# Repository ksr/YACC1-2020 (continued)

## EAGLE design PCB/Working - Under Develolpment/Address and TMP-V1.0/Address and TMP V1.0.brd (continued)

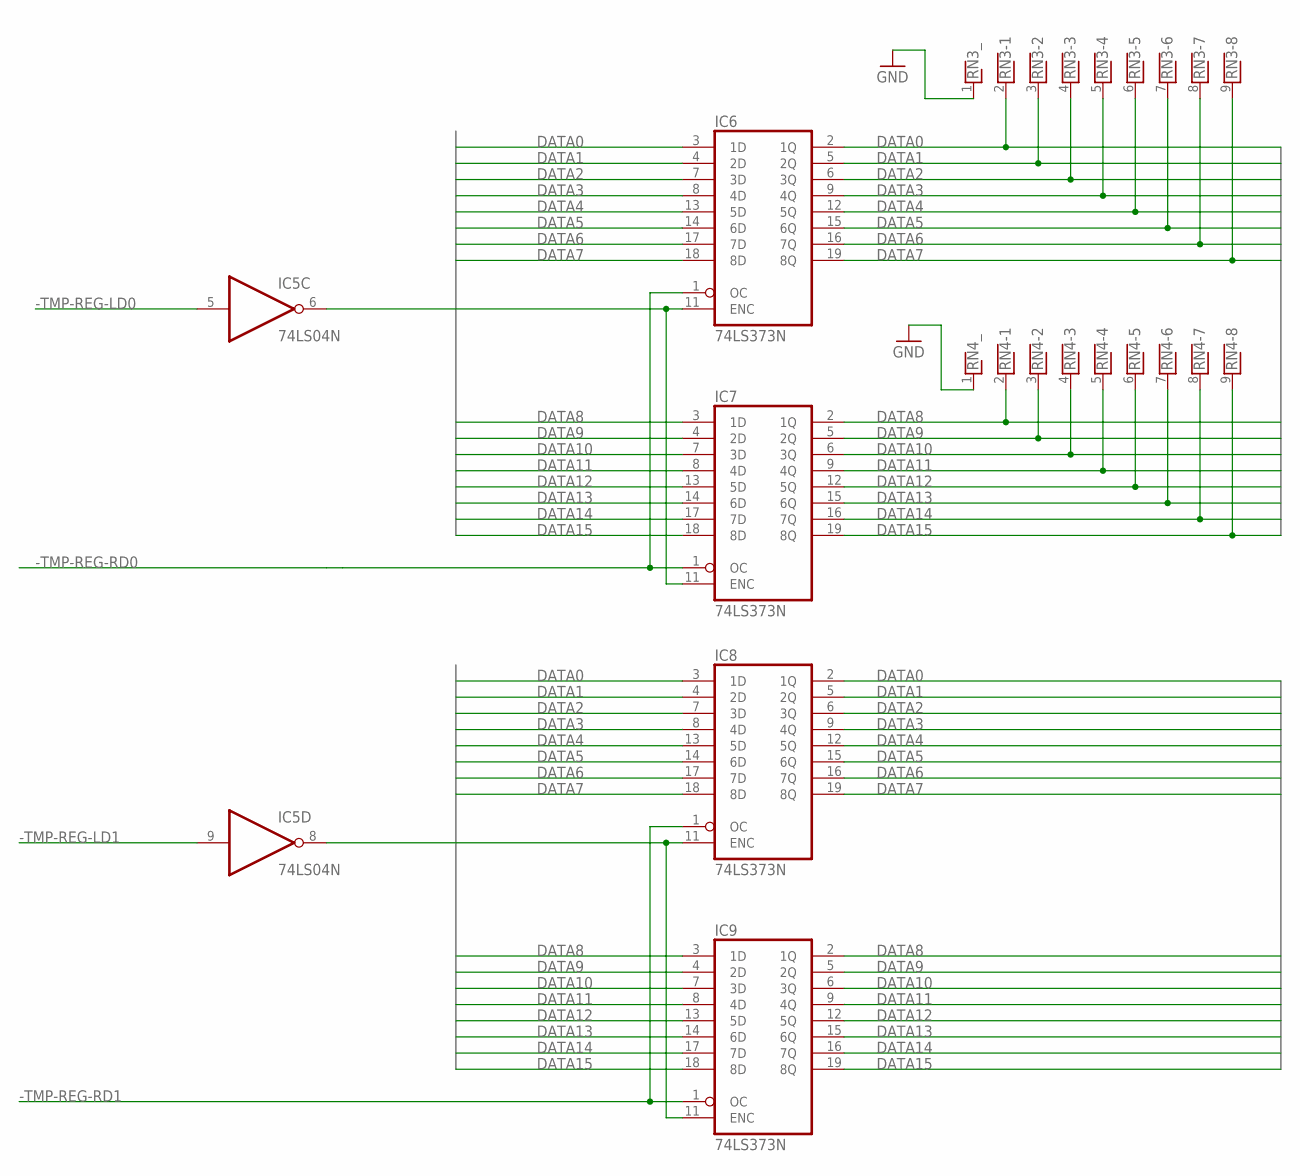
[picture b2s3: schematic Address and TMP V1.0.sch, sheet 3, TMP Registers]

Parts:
IC5: 74LS04N; DIL14
IC6, IC7, IC8, IC9: 74LS373N; DIL20
RN3, RN4: RNX8; RN-9

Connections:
-TMP-REG-LD0: IC5.5 (I); also elsewhere on the board
-TMP-REG-LD1: IC5.9 (I); also elsewhere on the board
-TMP-REG-RD0: IC6.1 (OC), IC7.1 (OC); also elsewhere on the board
-TMP-REG-RD1: IC8.1 (OC), IC9.1 (OC); also elsewhere on the board
DATA0: IC6.2 (1Q), IC6.3 (1D), IC8.2 (1Q), IC8.3 (1D), RN3.2; also elsewhere on the board
DATA1: IC6.4 (2D), IC6.5 (2Q), IC8.4 (2D), IC8.5 (2Q), RN3.3; also elsewhere on the board
DATA2: IC6.6 (3Q), IC6.7 (3D), IC8.6 (3Q), IC8.7 (3D), RN3.4; also elsewhere on the board
DATA3: IC6.8 (4D), IC6.9 (4Q), IC8.8 (4D), IC8.9 (4Q), RN3.5; also elsewhere on the board
DATA4: IC6.12 (5Q), IC6.13 (5D), IC8.12 (5Q), IC8.13 (5D), RN3.6; also elsewhere on the board
DATA5: IC6.14 (6D), IC6.15 (6Q), IC8.14 (6D), IC8.15 (6Q), RN3.7; also elsewhere on the board
DATA6: IC6.16 (7Q), IC6.17 (7D), IC8.16 (7Q), IC8.17 (7D), RN3.8; also elsewhere on the board
DATA7: IC6.18 (8D), IC6.19 (8Q), IC8.18 (8D), IC8.19 (8Q), RN3.9; also elsewhere on the board
DATA8: IC7.2 (1Q), IC7.3 (1D), IC9.2 (1Q), IC9.3 (1D), RN4.2; also elsewhere on the board
DATA9: IC7.4 (2D), IC7.5 (2Q), IC9.4 (2D), IC9.5 (2Q), RN4.3; also elsewhere on the board
DATA10: IC7.6 (3Q), IC7.7 (3D), IC9.6 (3Q), IC9.7 (3D), RN4.4; also elsewhere on the board
DATA11: IC7.8 (4D), IC7.9 (4Q), IC9.8 (4D), IC9.9 (4Q), RN4.5; also elsewhere on the board
DATA12: IC7.12 (5Q), IC7.13 (5D), IC9.12 (5Q), IC9.13 (5D), RN4.6; also elsewhere on the board
DATA13: IC7.14 (6D), IC7.15 (6Q), IC9.14 (6D), IC9.15 (6Q), RN4.7; also elsewhere on the board
DATA14: IC7.16 (7Q), IC7.17 (7D), IC9.16 (7Q), IC9.17 (7D), RN4.8; also elsewhere on the board
DATA15: IC7.18 (8D), IC7.19 (8Q), IC9.18 (8D), IC9.19 (8Q), RN4.9; also elsewhere on the board
GND: IC5.7 (GND), IC6.10 (GND), IC7.10 (GND), IC8.10 (GND), IC9.10 (GND), RN3.1, RN4.1; also elsewhere on the board
unnamed: IC5.6 (O), IC6.11 (ENC), IC7.11 (ENC)
unnamed: IC5.8 (O), IC8.11 (ENC), IC9.11 (ENC)
VCC: IC5.14 (VCC), IC6.20 (VCC), IC7.20 (VCC), IC8.20 (VCC), IC9.20 (VCC); also elsewhere on the board

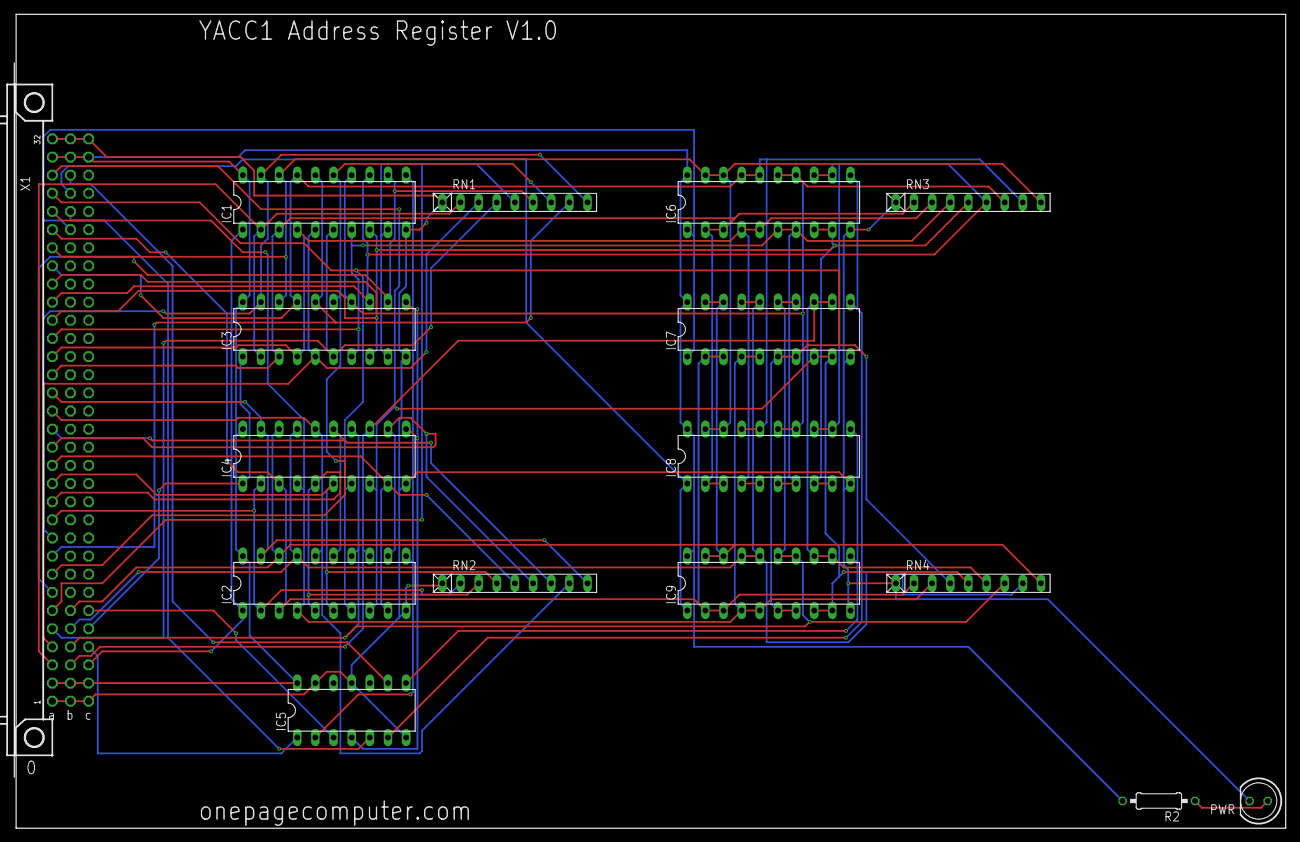
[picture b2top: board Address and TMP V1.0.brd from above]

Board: 2 copper layers, 177.8 x 114.0 mm, 16 parts (0 on the bottom side), 47 nets.

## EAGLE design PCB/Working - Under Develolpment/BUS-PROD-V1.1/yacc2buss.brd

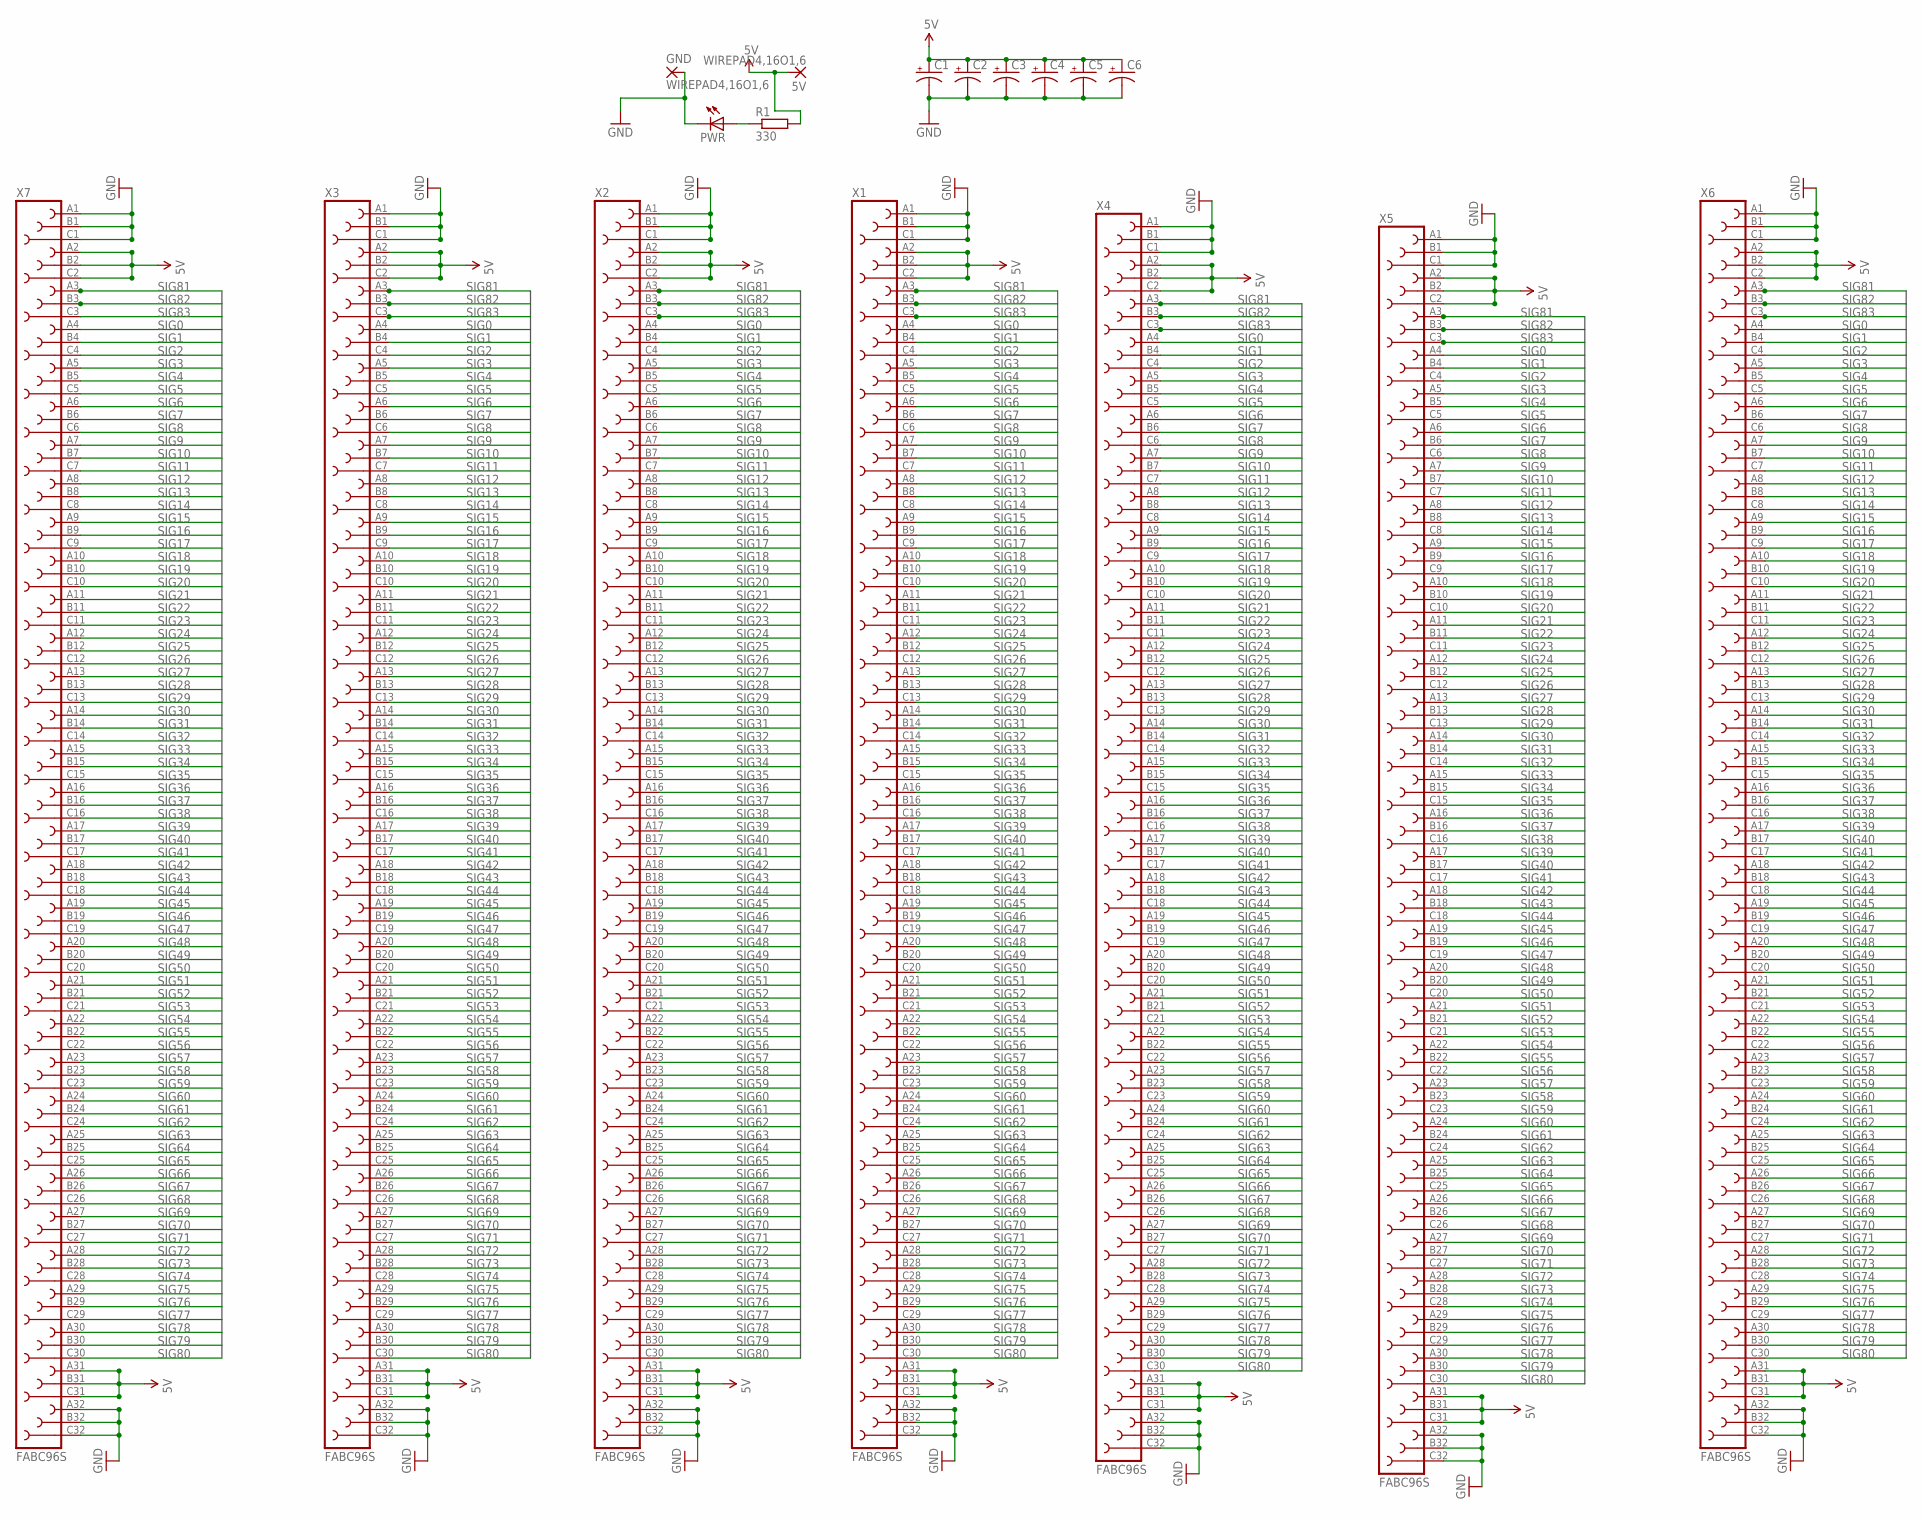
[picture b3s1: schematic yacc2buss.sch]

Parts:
5V: WIREPAD4,16O1,6; 4,16O1,6
C1, C2, C3, C4, C5, C6: CPOL-USE5-6; E5-6
GND: WIREPAD4,16O1,6; 4,16O1,6
PWR: LED5MM
R1: 330; 0207/10
X1, X2, X3, X4, X5, X6, X7: FABC96S

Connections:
5V: 5V.1, C1.+, C2.+, C3.+, C4.+, C5.+, C6.+, R1.2, X1.A2, X1.A31, X1.B2, X1.B31, X1.C2, X1.C31, X2.A2, X2.A31, X2.B2, X2.B31, X2.C2, X2.C31, X3.A2, X3.A31, X3.B2, X3.B31, X3.C2, X3.C31, X4.A2, X4.A31, X4.B2, X4.B31, X4.C2, X4.C31, X5.A2, X5.A31, X5.B2, X5.B31, X5.C2, X5.C31, X6.A2, X6.A31, X6.B2, X6.B31, X6.C2, X6.C31, X7.A2, X7.A31, X7.B2, X7.B31, X7.C2, X7.C31
GND: C1.-, C2.-, C3.-, C4.-, C5.-, C6.-, GND.1, PWR.K (C), X1.A1, X1.A32, X1.B1, X1.B32, X1.C1, X1.C32, X2.A1, X2.A32, X2.B1, X2.B32, X2.C1, X2.C32, X3.A1, X3.A32, X3.B1, X3.B32, X3.C1, X3.C32, X4.A1, X4.A32, X4.B1, X4.B32, X4.C1, X4.C32, X5.A1, X5.A32, X5.B1, X5.B32, X5.C1, X5.C32, X6.A1, X6.A32, X6.B1, X6.B32, X6.C1, X6.C32, X7.A1, X7.A32, X7.B1, X7.B32, X7.C1, X7.C32
unnamed: PWR.A, R1.1
SIG0: X1.A4, X2.A4, X3.A4, X4.A4, X5.A4, X6.A4, X7.A4
SIG1: X1.B4, X2.B4, X3.B4, X4.B4, X5.B4, X6.B4, X7.B4
SIG2: X1.C4, X2.C4, X3.C4, X4.C4, X5.C4, X6.C4, X7.C4
SIG3: X1.A5, X2.A5, X3.A5, X4.A5, X5.A5, X6.A5, X7.A5
SIG4: X1.B5, X2.B5, X3.B5, X4.B5, X5.B5, X6.B5, X7.B5
SIG5: X1.C5, X2.C5, X3.C5, X4.C5, X5.C5, X6.C5, X7.C5
SIG6: X1.A6, X2.A6, X3.A6, X4.A6, X5.A6, X6.A6, X7.A6
SIG7: X1.B6, X2.B6, X3.B6, X4.B6, X5.B6, X6.B6, X7.B6
SIG8: X1.C6, X2.C6, X3.C6, X4.C6, X5.C6, X6.C6, X7.C6
SIG9: X1.A7, X2.A7, X3.A7, X4.A7, X5.A7, X6.A7, X7.A7
SIG10: X1.B7, X2.B7, X3.B7, X4.B7, X5.B7, X6.B7, X7.B7
SIG11: X1.C7, X2.C7, X3.C7, X4.C7, X5.C7, X6.C7, X7.C7
SIG12: X1.A8, X2.A8, X3.A8, X4.A8, X5.A8, X6.A8, X7.A8
SIG13: X1.B8, X2.B8, X3.B8, X4.B8, X5.B8, X6.B8, X7.B8
SIG14: X1.C8, X2.C8, X3.C8, X4.C8, X5.C8, X6.C8, X7.C8
SIG15: X1.A9, X2.A9, X3.A9, X4.A9, X5.A9, X6.A9, X7.A9
SIG16: X1.B9, X2.B9, X3.B9, X4.B9, X5.B9, X6.B9, X7.B9
SIG17: X1.C9, X2.C9, X3.C9, X4.C9, X5.C9, X6.C9, X7.C9
SIG18: X1.A10, X2.A10, X3.A10, X4.A10, X5.A10, X6.A10, X7.A10
SIG19: X1.B10, X2.B10, X3.B10, X4.B10, X5.B10, X6.B10, X7.B10
SIG20: X1.C10, X2.C10, X3.C10, X4.C10, X5.C10, X6.C10, X7.C10
SIG21: X1.A11, X2.A11, X3.A11, X4.A11, X5.A11, X6.A11, X7.A11
SIG22: X1.B11, X2.B11, X3.B11, X4.B11, X5.B11, X6.B11, X7.B11
SIG23: X1.C11, X2.C11, X3.C11, X4.C11, X5.C11, X6.C11, X7.C11
SIG24: X1.A12, X2.A12, X3.A12, X4.A12, X5.A12, X6.A12, X7.A12
SIG25: X1.B12, X2.B12, X3.B12, X4.B12, X5.B12, X6.B12, X7.B12
SIG26: X1.C12, X2.C12, X3.C12, X4.C12, X5.C12, X6.C12, X7.C12
SIG27: X1.A13, X2.A13, X3.A13, X4.A13, X5.A13, X6.A13, X7.A13
SIG28: X1.B13, X2.B13, X3.B13, X4.B13, X5.B13, X6.B13, X7.B13
SIG29: X1.C13, X2.C13, X3.C13, X4.C13, X5.C13, X6.C13, X7.C13
SIG30: X1.A14, X2.A14, X3.A14, X4.A14, X5.A14, X6.A14, X7.A14
SIG31: X1.B14, X2.B14, X3.B14, X4.B14, X5.B14, X6.B14, X7.B14
SIG32: X1.C14, X2.C14, X3.C14, X4.C14, X5.C14, X6.C14, X7.C14
SIG33: X1.A15, X2.A15, X3.A15, X4.A15, X5.A15, X6.A15, X7.A15
SIG34: X1.B15, X2.B15, X3.B15, X4.B15, X5.B15, X6.B15, X7.B15
SIG35: X1.C15, X2.C15, X3.C15, X4.C15, X5.C15, X6.C15, X7.C15
SIG36: X1.A16, X2.A16, X3.A16, X4.A16, X5.A16, X6.A16, X7.A16
SIG37: X1.B16, X2.B16, X3.B16, X4.B16, X5.B16, X6.B16, X7.B16
SIG38: X1.C16, X2.C16, X3.C16, X4.C16, X5.C16, X6.C16, X7.C16
SIG39: X1.A17, X2.A17, X3.A17, X4.A17, X5.A17, X6.A17, X7.A17
SIG40: X1.B17, X2.B17, X3.B17, X4.B17, X5.B17, X6.B17, X7.B17
SIG41: X1.C17, X2.C17, X3.C17, X4.C17, X5.C17, X6.C17, X7.C17
SIG42: X1.A18, X2.A18, X3.A18, X4.A18, X5.A18, X6.A18, X7.A18
SIG43: X1.B18, X2.B18, X3.B18, X4.B18, X5.B18, X6.B18, X7.B18
SIG44: X1.C18, X2.C18, X3.C18, X4.C18, X5.C18, X6.C18, X7.C18
SIG45: X1.A19, X2.A19, X3.A19, X4.A19, X5.A19, X6.A19, X7.A19
SIG46: X1.B19, X2.B19, X3.B19, X4.B19, X5.B19, X6.B19, X7.B19
SIG47: X1.C19, X2.C19, X3.C19, X4.C19, X5.C19, X6.C19, X7.C19
SIG48: X1.A20, X2.A20, X3.A20, X4.A20, X5.A20, X6.A20, X7.A20
SIG49: X1.B20, X2.B20, X3.B20, X4.B20, X5.B20, X6.B20, X7.B20
SIG50: X1.C20, X2.C20, X3.C20, X4.C20, X5.C20, X6.C20, X7.C20
SIG51: X1.A21, X2.A21, X3.A21, X4.A21, X5.A21, X6.A21, X7.A21
SIG52: X1.B21, X2.B21, X3.B21, X4.B21, X5.B21, X6.B21, X7.B21
SIG53: X1.C21, X2.C21, X3.C21, X4.C21, X5.C21, X6.C21, X7.C21
SIG54: X1.A22, X2.A22, X3.A22, X4.A22, X5.A22, X6.A22, X7.A22
SIG55: X1.B22, X2.B22, X3.B22, X4.B22, X5.B22, X6.B22, X7.B22
SIG56: X1.C22, X2.C22, X3.C22, X4.C22, X5.C22, X6.C22, X7.C22
SIG57: X1.A23, X2.A23, X3.A23, X4.A23, X5.A23, X6.A23, X7.A23
SIG58: X1.B23, X2.B23, X3.B23, X4.B23, X5.B23, X6.B23, X7.B23
SIG59: X1.C23, X2.C23, X3.C23, X4.C23, X5.C23, X6.C23, X7.C23
SIG60: X1.A24, X2.A24, X3.A24, X4.A24, X5.A24, X6.A24, X7.A24
SIG61: X1.B24, X2.B24, X3.B24, X4.B24, X5.B24, X6.B24, X7.B24
SIG62: X1.C24, X2.C24, X3.C24, X4.C24, X5.C24, X6.C24, X7.C24
SIG63: X1.A25, X2.A25, X3.A25, X4.A25, X5.A25, X6.A25, X7.A25
SIG64: X1.B25, X2.B25, X3.B25, X4.B25, X5.B25, X6.B25, X7.B25
SIG65: X1.C25, X2.C25, X3.C25, X4.C25, X5.C25, X6.C25, X7.C25
SIG66: X1.A26, X2.A26, X3.A26, X4.A26, X5.A26, X6.A26, X7.A26
SIG67: X1.B26, X2.B26, X3.B26, X4.B26, X5.B26, X6.B26, X7.B26
SIG68: X1.C26, X2.C26, X3.C26, X4.C26, X5.C26, X6.C26, X7.C26
SIG69: X1.A27, X2.A27, X3.A27, X4.A27, X5.A27, X6.A27, X7.A27
SIG70: X1.B27, X2.B27, X3.B27, X4.B27, X5.B27, X6.B27, X7.B27
SIG71: X1.C27, X2.C27, X3.C27, X4.C27, X5.C27, X6.C27, X7.C27
SIG72: X1.A28, X2.A28, X3.A28, X4.A28, X5.A28, X6.A28, X7.A28
SIG73: X1.B28, X2.B28, X3.B28, X4.B28, X5.B28, X6.B28, X7.B28
SIG74: X1.C28, X2.C28, X3.C28, X4.C28, X5.C28, X6.C28, X7.C28
SIG75: X1.A29, X2.A29, X3.A29, X4.A29, X5.A29, X6.A29, X7.A29
SIG76: X1.B29, X2.B29, X3.B29, X4.B29, X5.B29, X6.B29, X7.B29
SIG77: X1.C29, X2.C29, X3.C29, X4.C29, X5.C29, X6.C29, X7.C29
SIG78: X1.A30, X2.A30, X3.A30, X4.A30, X5.A30, X6.A30, X7.A30
SIG79: X1.B30, X2.B30, X3.B30, X4.B30, X5.B30, X6.B30, X7.B30
SIG80: X1.C30, X2.C30, X3.C30, X4.C30, X5.C30, X6.C30, X7.C30
SIG81: X1.A3, X2.A3, X3.A3, X4.A3, X5.A3, X6.A3, X7.A3
SIG82: X1.B3, X2.B3, X3.B3, X4.B3, X5.B3, X6.B3, X7.B3
SIG83: X1.C3, X2.C3, X3.C3, X4.C3, X5.C3, X6.C3, X7.C3

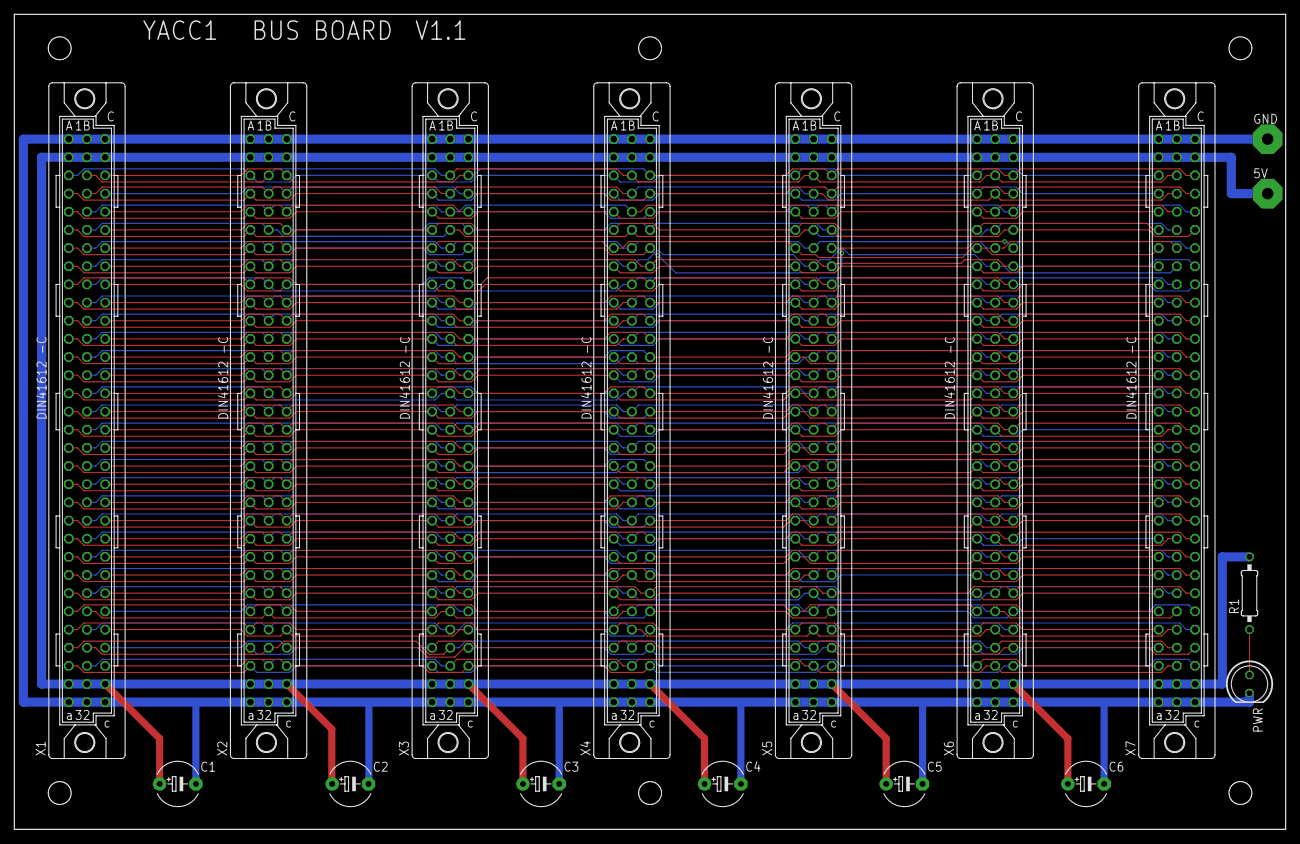
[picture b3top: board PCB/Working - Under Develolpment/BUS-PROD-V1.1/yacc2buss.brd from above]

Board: 2 copper layers, 177.8 x 114.0 mm, 17 parts (0 on the bottom side), 87 nets.

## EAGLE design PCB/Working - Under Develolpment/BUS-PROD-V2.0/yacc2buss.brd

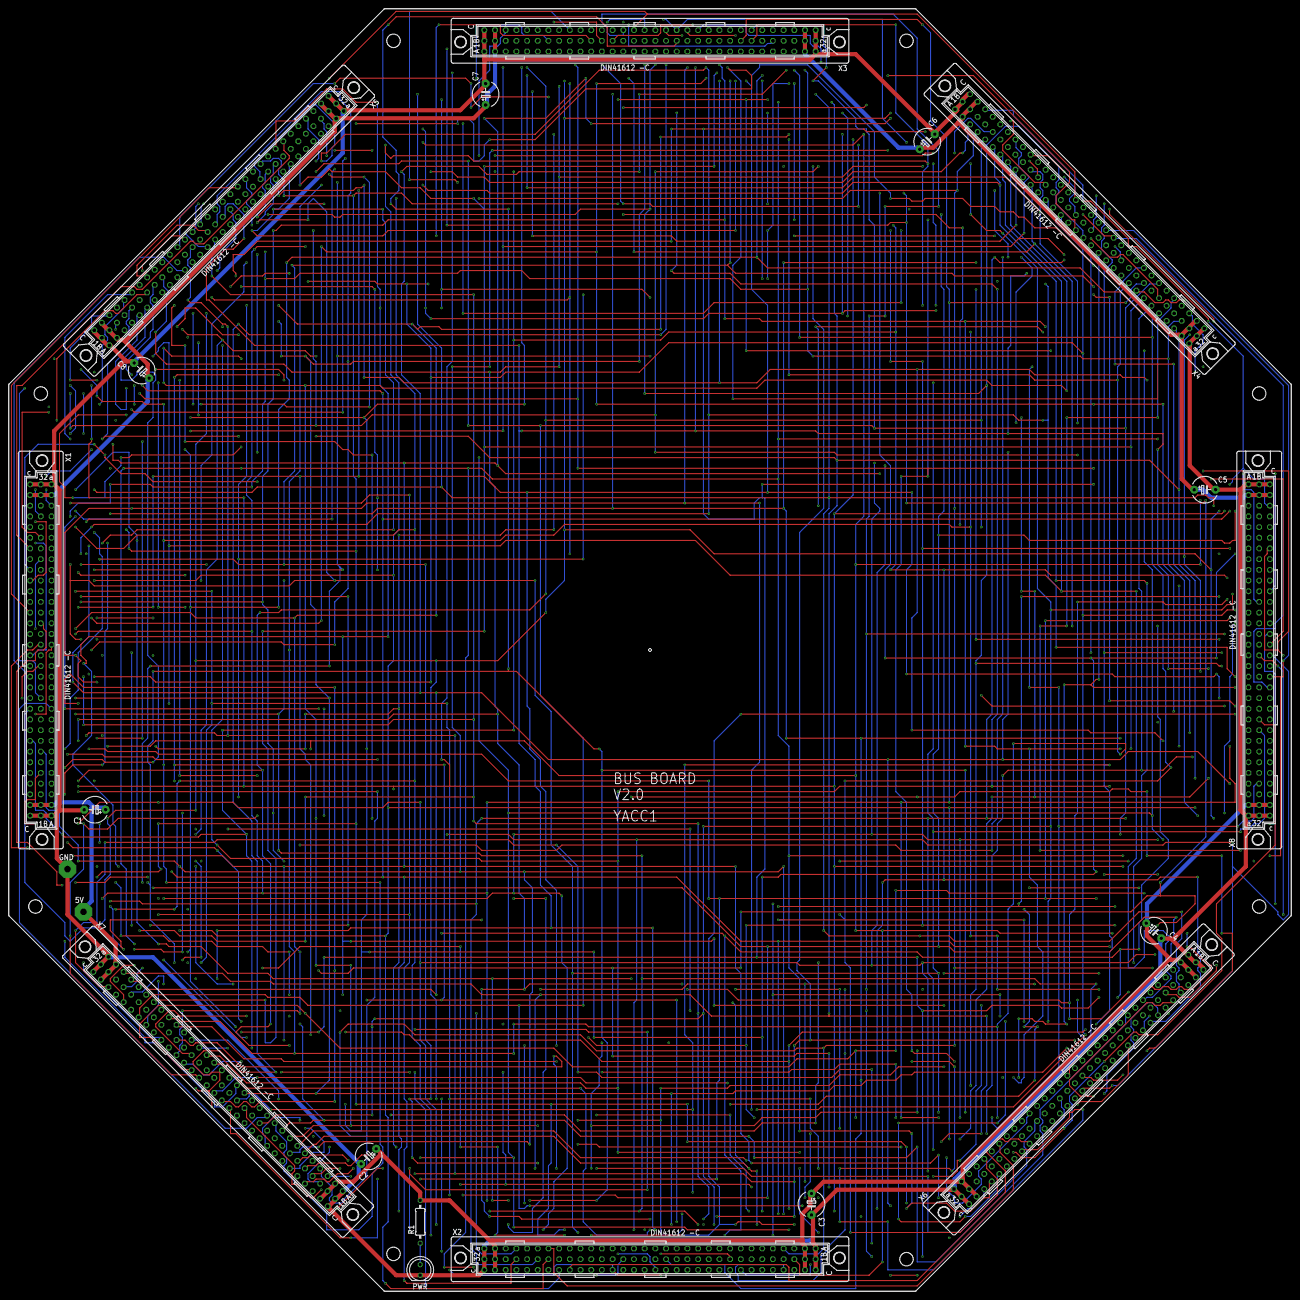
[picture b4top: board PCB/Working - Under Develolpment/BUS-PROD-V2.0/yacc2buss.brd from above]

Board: 4 copper layers, 304.8 x 304.8 mm, 20 parts (0 on the bottom side), 87 nets.

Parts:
5V: WIREPAD4,16O1,6; 4,16O1,6
C1, C2, C3, C4, C5, C6, C7, C8: E5-6
GND: WIREPAD4,16O1,6; 4,16O1,6
PWR: LED5MM
R1: 330; 0207/10
X1, X2, X3, X4, X5, X6, X7, X8: FABC96S

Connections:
5V: 5V.1, C1.+, C2.+, C3.+, C4.+, C5.+, C6.+, C7.+, C8.+, R1.2, X1.A2, X1.A31, X1.B2, X1.B31, X1.C2, X1.C31, X2.A2, X2.A31, X2.B2, X2.B31, X2.C2, X2.C31, X3.A2, X3.A31, X3.B2, X3.B31, X3.C2, X3.C31, X4.A2, X4.A31, X4.B2, X4.B31, X4.C2, X4.C31, X5.A2, X5.A31, X5.B2, X5.B31, X5.C2, X5.C31, X6.A2, X6.A31, X6.B2, X6.B31, X6.C2, X6.C31, X7.A2, X7.A31, X7.B2, X7.B31, X7.C2, X7.C31, X8.A2, X8.A31, X8.B2, X8.B31, X8.C2, X8.C31
GND: C1.-, C2.-, C3.-, C4.-, C5.-, C6.-, C7.-, C8.-, GND.1, PWR.K, X1.A1, X1.A32, X1.B1, X1.B32, X1.C1, X1.C32, X2.A1, X2.A32, X2.B1, X2.B32, X2.C1, X2.C32, X3.A1, X3.A32, X3.B1, X3.B32, X3.C1, X3.C32, X4.A1, X4.A32, X4.B1, X4.B32, X4.C1, X4.C32, X5.A1, X5.A32, X5.B1, X5.B32, X5.C1, X5.C32, X6.A1, X6.A32, X6.B1, X6.B32, X6.C1, X6.C32, X7.A1, X7.A32, X7.B1, X7.B32, X7.C1, X7.C32, X8.A1, X8.A32, X8.B1, X8.B32, X8.C1, X8.C32
unnamed: PWR.A, R1.1
SIG0: X1.A4, X2.A4, X3.A4, X4.A4, X5.A4, X6.A4, X7.A4, X8.A4
SIG1: X1.B4, X2.B4, X3.B4, X4.B4, X5.B4, X6.B4, X7.B4, X8.B4
SIG2: X1.C4, X2.C4, X3.C4, X4.C4, X5.C4, X6.C4, X7.C4, X8.C4
SIG3: X1.A5, X2.A5, X3.A5, X4.A5, X5.A5, X6.A5, X7.A5, X8.A5
SIG4: X1.B5, X2.B5, X3.B5, X4.B5, X5.B5, X6.B5, X7.B5, X8.B5
SIG5: X1.C5, X2.C5, X3.C5, X4.C5, X5.C5, X6.C5, X7.C5, X8.C5
SIG6: X1.A6, X2.A6, X3.A6, X4.A6, X5.A6, X6.A6, X7.A6, X8.A6
SIG7: X1.B6, X2.B6, X3.B6, X4.B6, X5.B6, X6.B6, X7.B6, X8.B6
SIG8: X1.C6, X2.C6, X3.C6, X4.C6, X5.C6, X6.C6, X7.C6, X8.C6
SIG9: X1.A7, X2.A7, X3.A7, X4.A7, X5.A7, X6.A7, X7.A7, X8.A7
SIG10: X1.B7, X2.B7, X3.B7, X4.B7, X5.B7, X6.B7, X7.B7, X8.B7
SIG11: X1.C7, X2.C7, X3.C7, X4.C7, X5.C7, X6.C7, X7.C7, X8.C7
SIG12: X1.A8, X2.A8, X3.A8, X4.A8, X5.A8, X6.A8, X7.A8, X8.A8
SIG13: X1.B8, X2.B8, X3.B8, X4.B8, X5.B8, X6.B8, X7.B8, X8.B8
SIG14: X1.C8, X2.C8, X3.C8, X4.C8, X5.C8, X6.C8, X7.C8, X8.C8
SIG15: X1.A9, X2.A9, X3.A9, X4.A9, X5.A9, X6.A9, X7.A9, X8.A9
SIG16: X1.B9, X2.B9, X3.B9, X4.B9, X5.B9, X6.B9, X7.B9, X8.B9
SIG17: X1.C9, X2.C9, X3.C9, X4.C9, X5.C9, X6.C9, X7.C9, X8.C9
SIG18: X1.A10, X2.A10, X3.A10, X4.A10, X5.A10, X6.A10, X7.A10, X8.A10
SIG19: X1.B10, X2.B10, X3.B10, X4.B10, X5.B10, X6.B10, X7.B10, X8.B10
SIG20: X1.C10, X2.C10, X3.C10, X4.C10, X5.C10, X6.C10, X7.C10, X8.C10
SIG21: X1.A11, X2.A11, X3.A11, X4.A11, X5.A11, X6.A11, X7.A11, X8.A11
SIG22: X1.B11, X2.B11, X3.B11, X4.B11, X5.B11, X6.B11, X7.B11, X8.B11
SIG23: X1.C11, X2.C11, X3.C11, X4.C11, X5.C11, X6.C11, X7.C11, X8.C11
SIG24: X1.A12, X2.A12, X3.A12, X4.A12, X5.A12, X6.A12, X7.A12, X8.A12
SIG25: X1.B12, X2.B12, X3.B12, X4.B12, X5.B12, X6.B12, X7.B12, X8.B12
SIG26: X1.C12, X2.C12, X3.C12, X4.C12, X5.C12, X6.C12, X7.C12, X8.C12
SIG27: X1.A13, X2.A13, X3.A13, X4.A13, X5.A13, X6.A13, X7.A13, X8.A13
SIG28: X1.B13, X2.B13, X3.B13, X4.B13, X5.B13, X6.B13, X7.B13, X8.B13
SIG29: X1.C13, X2.C13, X3.C13, X4.C13, X5.C13, X6.C13, X7.C13, X8.C13
SIG30: X1.A14, X2.A14, X3.A14, X4.A14, X5.A14, X6.A14, X7.A14, X8.A14
SIG31: X1.B14, X2.B14, X3.B14, X4.B14, X5.B14, X6.B14, X7.B14, X8.B14
SIG32: X1.C14, X2.C14, X3.C14, X4.C14, X5.C14, X6.C14, X7.C14, X8.C14
SIG33: X1.A15, X2.A15, X3.A15, X4.A15, X5.A15, X6.A15, X7.A15, X8.A15
SIG34: X1.B15, X2.B15, X3.B15, X4.B15, X5.B15, X6.B15, X7.B15, X8.B15
SIG35: X1.C15, X2.C15, X3.C15, X4.C15, X5.C15, X6.C15, X7.C15, X8.C15
SIG36: X1.A16, X2.A16, X3.A16, X4.A16, X5.A16, X6.A16, X7.A16, X8.A16
SIG37: X1.B16, X2.B16, X3.B16, X4.B16, X5.B16, X6.B16, X7.B16, X8.B16
SIG38: X1.C16, X2.C16, X3.C16, X4.C16, X5.C16, X6.C16, X7.C16, X8.C16
SIG39: X1.A17, X2.A17, X3.A17, X4.A17, X5.A17, X6.A17, X7.A17, X8.A17
SIG40: X1.B17, X2.B17, X3.B17, X4.B17, X5.B17, X6.B17, X7.B17, X8.B17
SIG41: X1.C17, X2.C17, X3.C17, X4.C17, X5.C17, X6.C17, X7.C17, X8.C17
SIG42: X1.A18, X2.A18, X3.A18, X4.A18, X5.A18, X6.A18, X7.A18, X8.A18
SIG43: X1.B18, X2.B18, X3.B18, X4.B18, X5.B18, X6.B18, X7.B18, X8.B18
SIG44: X1.C18, X2.C18, X3.C18, X4.C18, X5.C18, X6.C18, X7.C18, X8.C18
SIG45: X1.A19, X2.A19, X3.A19, X4.A19, X5.A19, X6.A19, X7.A19, X8.A19
SIG46: X1.B19, X2.B19, X3.B19, X4.B19, X5.B19, X6.B19, X7.B19, X8.B19
SIG47: X1.C19, X2.C19, X3.C19, X4.C19, X5.C19, X6.C19, X7.C19, X8.C19
SIG48: X1.A20, X2.A20, X3.A20, X4.A20, X5.A20, X6.A20, X7.A20, X8.A20
SIG49: X1.B20, X2.B20, X3.B20, X4.B20, X5.B20, X6.B20, X7.B20, X8.B20
SIG50: X1.C20, X2.C20, X3.C20, X4.C20, X5.C20, X6.C20, X7.C20, X8.C20
SIG51: X1.A21, X2.A21, X3.A21, X4.A21, X5.A21, X6.A21, X7.A21, X8.A21
SIG52: X1.B21, X2.B21, X3.B21, X4.B21, X5.B21, X6.B21, X7.B21, X8.B21
SIG53: X1.C21, X2.C21, X3.C21, X4.C21, X5.C21, X6.C21, X7.C21, X8.C21
SIG54: X1.A22, X2.A22, X3.A22, X4.A22, X5.A22, X6.A22, X7.A22, X8.A22
SIG55: X1.B22, X2.B22, X3.B22, X4.B22, X5.B22, X6.B22, X7.B22, X8.B22
SIG56: X1.C22, X2.C22, X3.C22, X4.C22, X5.C22, X6.C22, X7.C22, X8.C22
SIG57: X1.A23, X2.A23, X3.A23, X4.A23, X5.A23, X6.A23, X7.A23, X8.A23
SIG58: X1.B23, X2.B23, X3.B23, X4.B23, X5.B23, X6.B23, X7.B23, X8.B23
SIG59: X1.C23, X2.C23, X3.C23, X4.C23, X5.C23, X6.C23, X7.C23, X8.C23
SIG60: X1.A24, X2.A24, X3.A24, X4.A24, X5.A24, X6.A24, X7.A24, X8.A24
SIG61: X1.B24, X2.B24, X3.B24, X4.B24, X5.B24, X6.B24, X7.B24, X8.B24
SIG62: X1.C24, X2.C24, X3.C24, X4.C24, X5.C24, X6.C24, X7.C24, X8.C24
SIG63: X1.A25, X2.A25, X3.A25, X4.A25, X5.A25, X6.A25, X7.A25, X8.A25
SIG64: X1.B25, X2.B25, X3.B25, X4.B25, X5.B25, X6.B25, X7.B25, X8.B25
SIG65: X1.C25, X2.C25, X3.C25, X4.C25, X5.C25, X6.C25, X7.C25, X8.C25
SIG66: X1.A26, X2.A26, X3.A26, X4.A26, X5.A26, X6.A26, X7.A26, X8.A26
SIG67: X1.B26, X2.B26, X3.B26, X4.B26, X5.B26, X6.B26, X7.B26, X8.B26
SIG68: X1.C26, X2.C26, X3.C26, X4.C26, X5.C26, X6.C26, X7.C26, X8.C26
SIG69: X1.A27, X2.A27, X3.A27, X4.A27, X5.A27, X6.A27, X7.A27, X8.A27
SIG70: X1.B27, X2.B27, X3.B27, X4.B27, X5.B27, X6.B27, X7.B27, X8.B27
SIG71: X1.C27, X2.C27, X3.C27, X4.C27, X5.C27, X6.C27, X7.C27, X8.C27
SIG72: X1.A28, X2.A28, X3.A28, X4.A28, X5.A28, X6.A28, X7.A28, X8.A28
SIG73: X1.B28, X2.B28, X3.B28, X4.B28, X5.B28, X6.B28, X7.B28, X8.B28
SIG74: X1.C28, X2.C28, X3.C28, X4.C28, X5.C28, X6.C28, X7.C28, X8.C28
SIG75: X1.A29, X2.A29, X3.A29, X4.A29, X5.A29, X6.A29, X7.A29, X8.A29
SIG76: X1.B29, X2.B29, X3.B29, X4.B29, X5.B29, X6.B29, X7.B29, X8.B29
SIG77: X1.C29, X2.C29, X3.C29, X4.C29, X5.C29, X6.C29, X7.C29, X8.C29
SIG78: X1.A30, X2.A30, X3.A30, X4.A30, X5.A30, X6.A30, X7.A30, X8.A30
SIG79: X1.B30, X2.B30, X3.B30, X4.B30, X5.B30, X6.B30, X7.B30, X8.B30
SIG80: X1.C30, X2.C30, X3.C30, X4.C30, X5.C30, X6.C30, X7.C30, X8.C30
SIG81: X1.A3, X2.A3, X3.A3, X4.A3, X5.A3, X6.A3, X7.A3, X8.A3
SIG82: X1.B3, X2.B3, X3.B3, X4.B3, X5.B3, X6.B3, X7.B3, X8.B3
SIG83: X1.C3, X2.C3, X3.C3, X4.C3, X5.C3, X6.C3, X7.C3, X8.C3

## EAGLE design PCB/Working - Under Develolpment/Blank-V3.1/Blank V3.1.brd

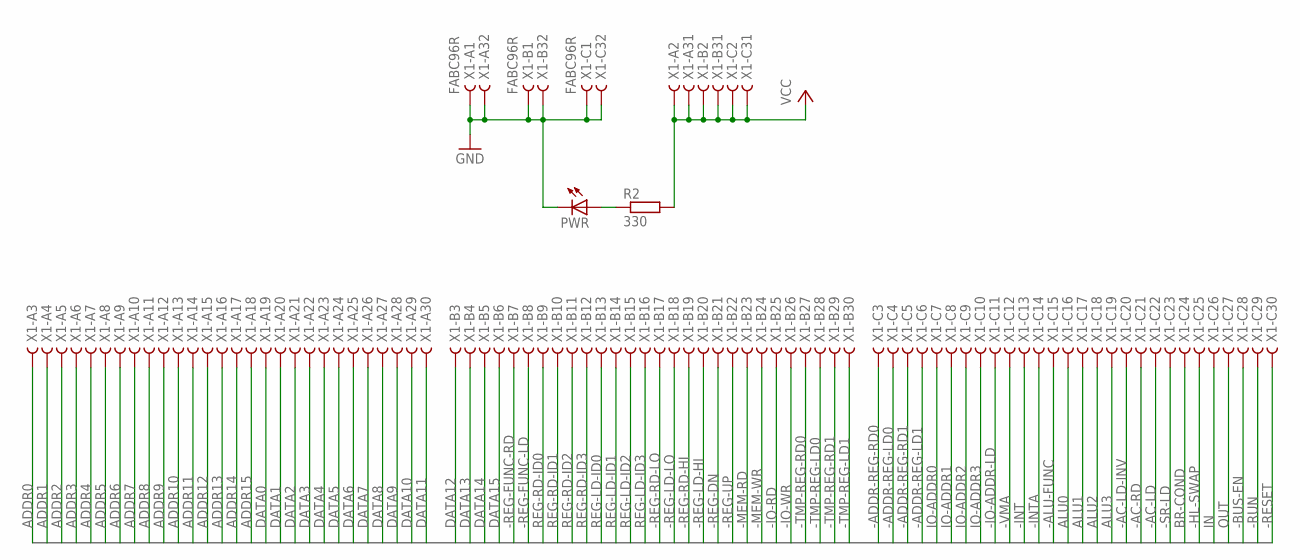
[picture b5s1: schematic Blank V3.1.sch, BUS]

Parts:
PWR: LED5MM
R2: 330; 0207/10
X1: FABC96R

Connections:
-AC-LD: X1.C22
-AC-LD-INV: X1.C20
-AC-RD: X1.C21
-ADDR-REG-LD0: X1.C4
-ADDR-REG-LD1: X1.C6
-ADDR-REG-RD0: X1.C3
-ADDR-REG-RD1: X1.C5
-ALU-FUNC: X1.C15
-BUS-EN: X1.C28
-HL-SWAP: X1.C25
-INT: X1.C13
-INTA: X1.C14
-IO-ADDR-LD: X1.C11
-IO-RD: X1.B25
-IO-WR: X1.B26
-MEM-RD: X1.B23
-MEM-WR: X1.B24
-REG-DN: X1.B21
-REG-FUNC-LD: X1.B8
-REG-FUNC-RD: X1.B7
-REG-LD-HI: X1.B20
-REG-LD-LO: X1.B18
-REG-RD-HI: X1.B19
-REG-RD-LO: X1.B17
-REG-UP: X1.B22
-RESET: X1.C30
-RUN: X1.C29
-SR-LD: X1.C23
-TMP-REG-LD0: X1.B28
-TMP-REG-LD1: X1.B30
-TMP-REG-RD0: X1.B27
-TMP-REG-RD1: X1.B29
-VMA: X1.C12
ADDR0: X1.A3
ADDR1: X1.A4
ADDR2: X1.A5
ADDR3: X1.A6
ADDR4: X1.A7
ADDR5: X1.A8
ADDR6: X1.A9
ADDR7: X1.A10
ADDR8: X1.A11
ADDR9: X1.A12
ADDR10: X1.A13
ADDR11: X1.A14
ADDR12: X1.A15
ADDR13: X1.A16
ADDR14: X1.A17
ADDR15: X1.A18
ALU0: X1.C16
ALU1: X1.C17
ALU2: X1.C18
ALU3: X1.C19
BR-COND: X1.C24
DATA0: X1.A19
DATA1: X1.A20
DATA2: X1.A21
DATA3: X1.A22
DATA4: X1.A23
DATA5: X1.A24
DATA6: X1.A25
DATA7: X1.A26
DATA8: X1.A27
DATA9: X1.A28
DATA10: X1.A29
DATA11: X1.A30
DATA12: X1.B3
DATA13: X1.B4
DATA14: X1.B5
DATA15: X1.B6
GND: PWR.K (C), X1.A1, X1.A32, X1.B1, X1.B32, X1.C1, X1.C32
IN: X1.C26
IO-ADDR0: X1.C7
IO-ADDR1: X1.C8
IO-ADDR2: X1.C9
IO-ADDR3: X1.C10
unnamed: PWR.A, R2.1
OUT: X1.C27
REG-LD-ID0: X1.B13
REG-LD-ID1: X1.B14
REG-LD-ID2: X1.B15
REG-LD-ID3: X1.B16
REG-RD-ID0: X1.B9
REG-RD-ID1: X1.B10
REG-RD-ID2: X1.B11
REG-RD-ID3: X1.B12
VCC: R2.2, X1.A2, X1.A31, X1.B2, X1.B31, X1.C2, X1.C31

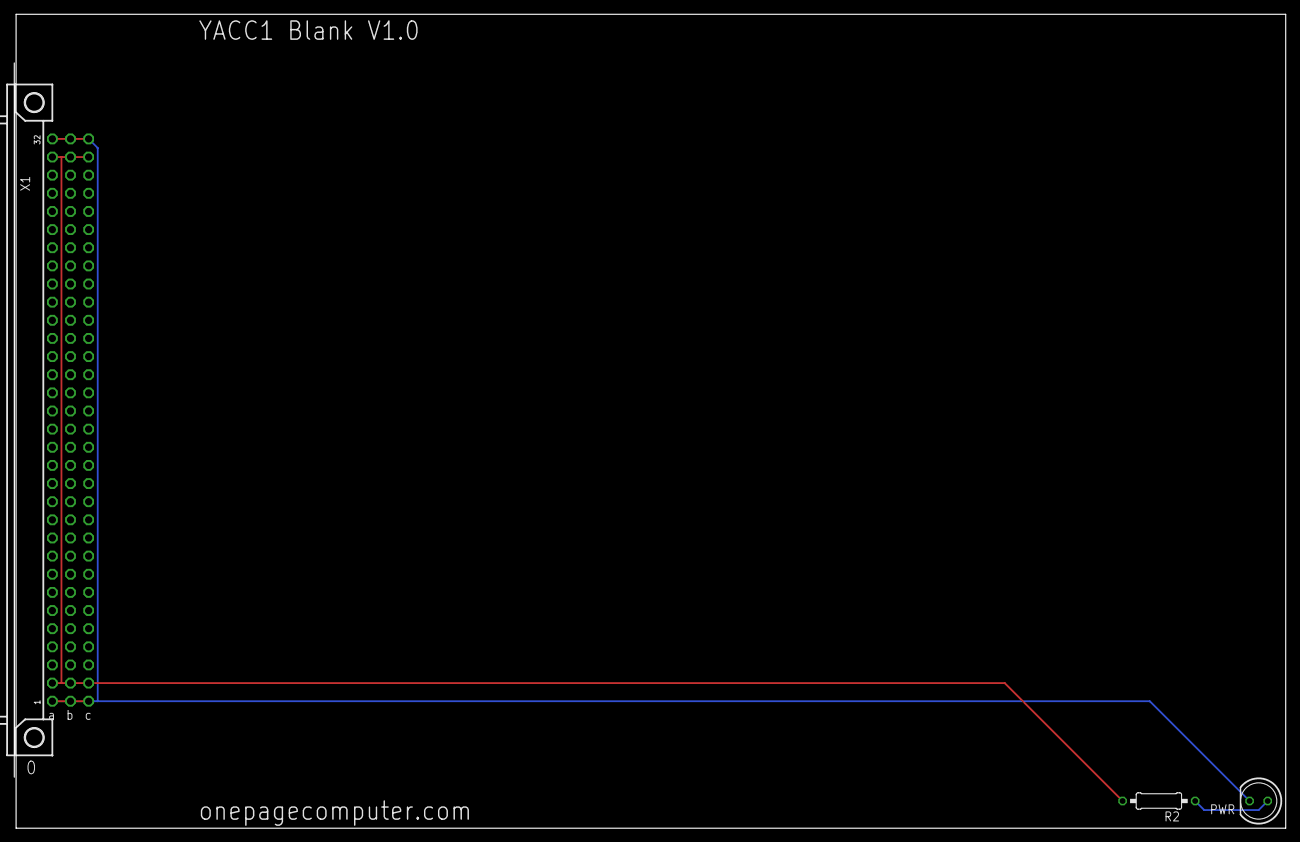
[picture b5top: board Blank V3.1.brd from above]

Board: 2 copper layers, 177.8 x 114.0 mm, 3 parts (0 on the bottom side), 3 nets.
